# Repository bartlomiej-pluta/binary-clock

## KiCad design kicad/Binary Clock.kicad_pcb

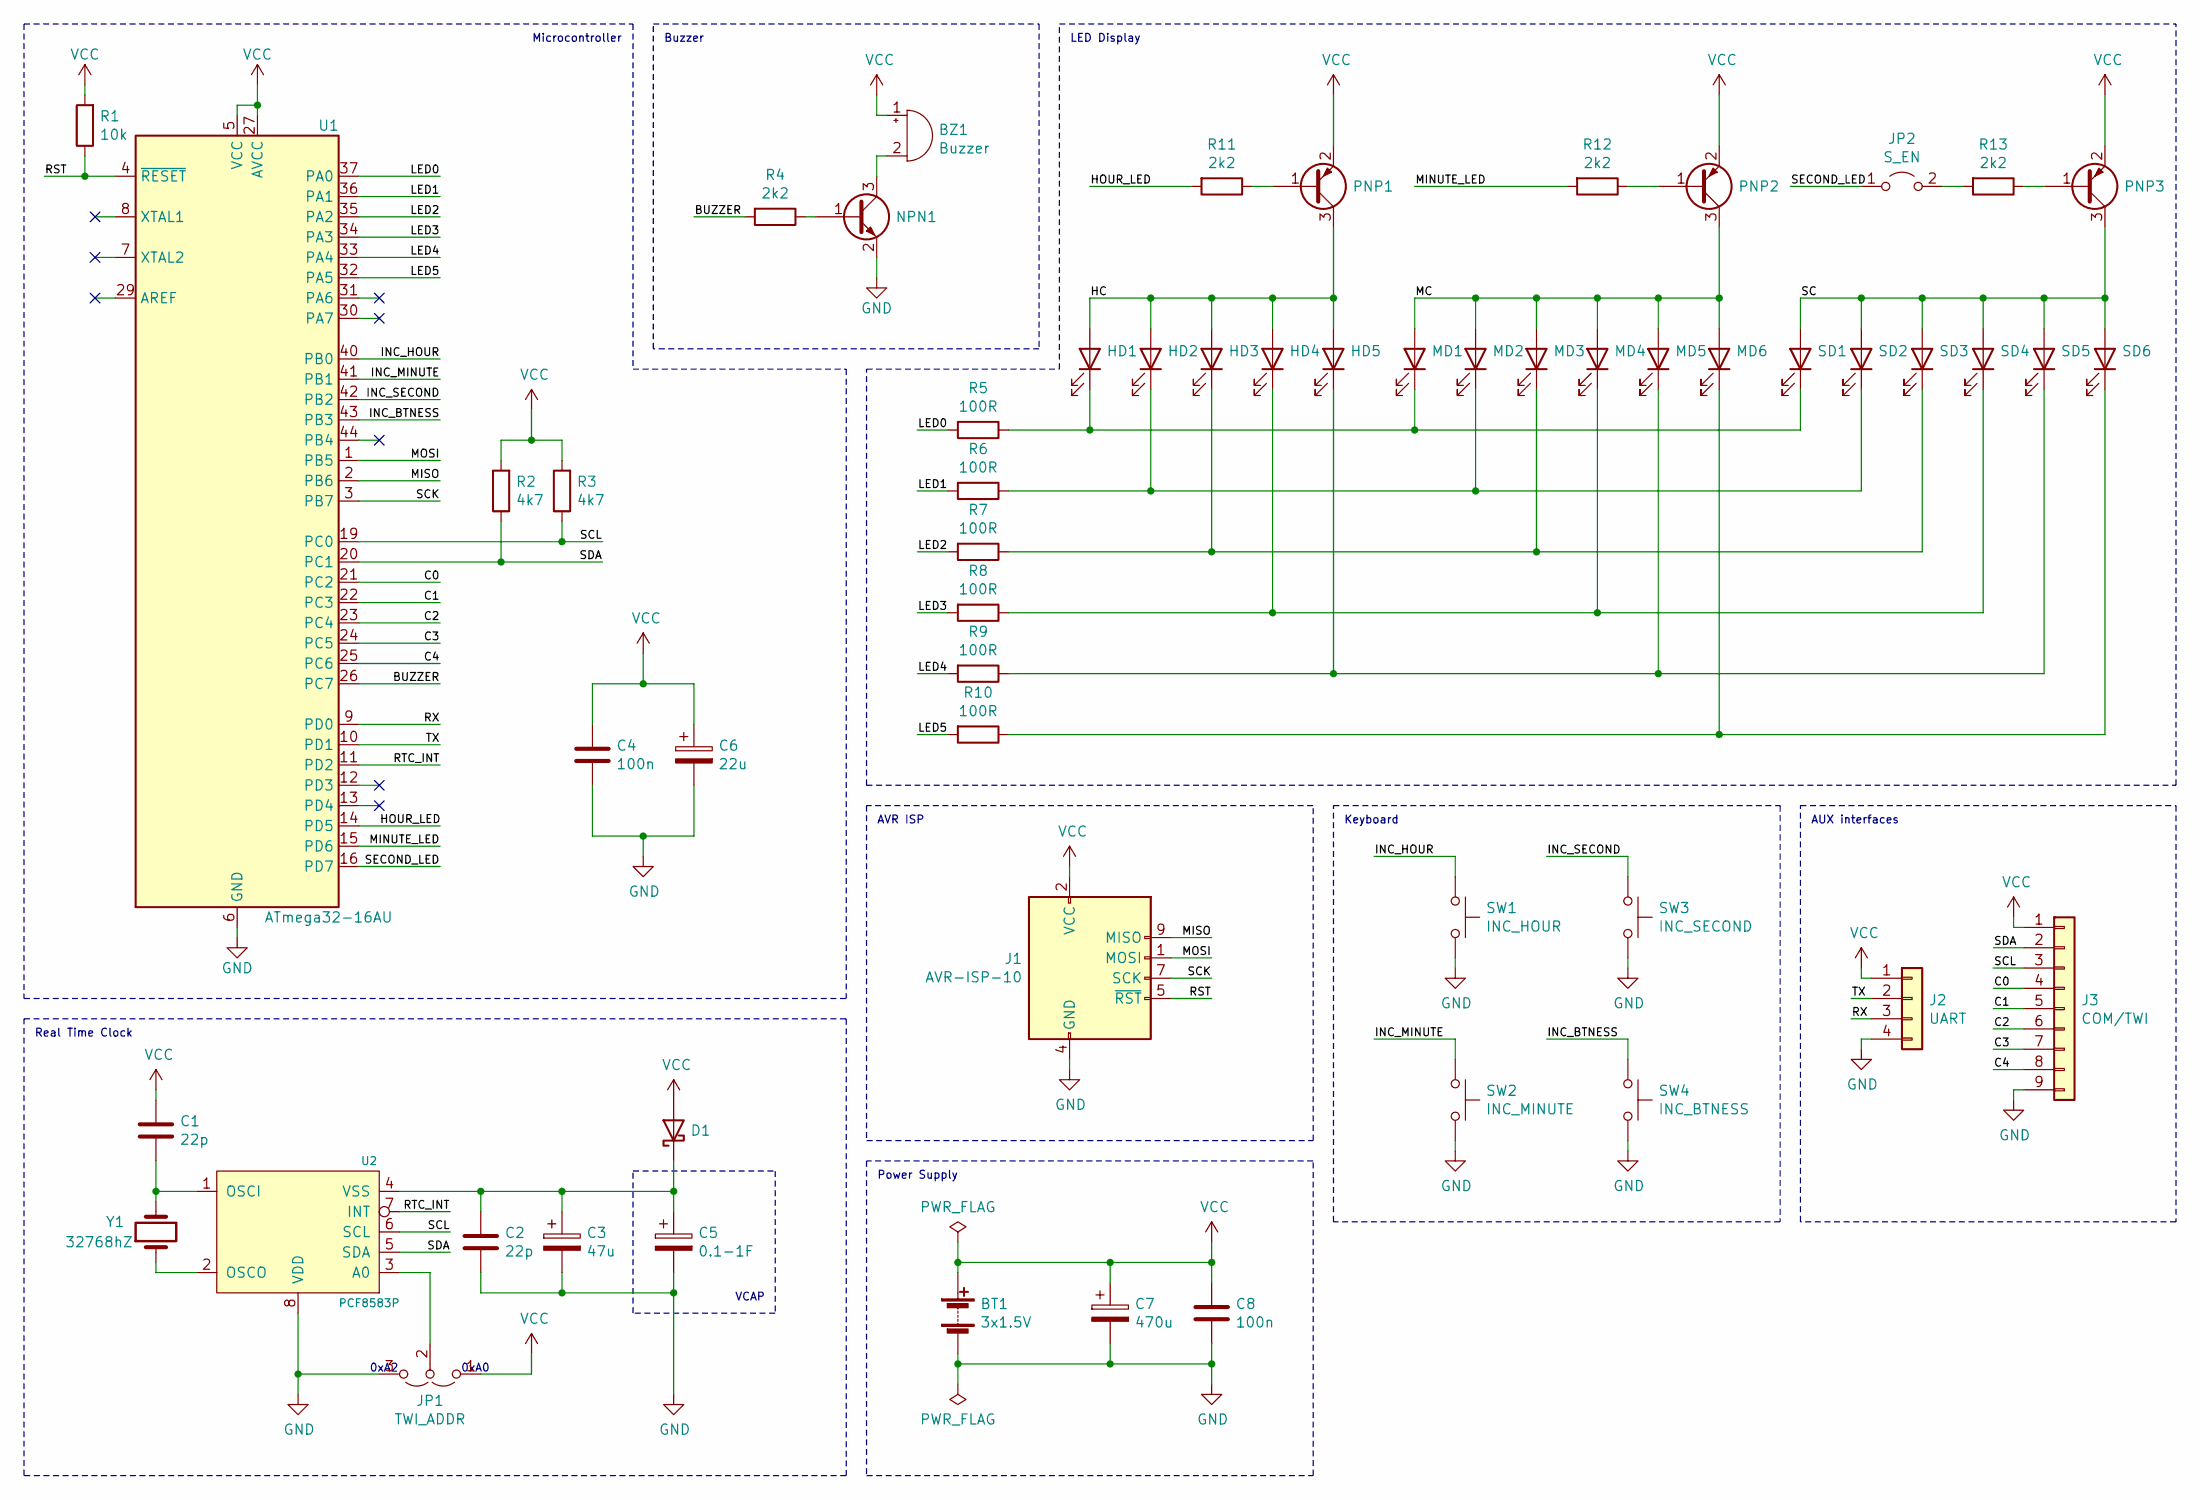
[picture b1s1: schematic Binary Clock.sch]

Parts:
BT1: 3x1.5V; BatteryPackage
BZ1: Buzzer; Buzzer_12x9.5RM7.6
C1, C2: 22p; C_0805_2012Metric_Pad1.18x1.45mm_HandSolder
C3: 47u; CP_Elec_6.3x5.3
C4, C8: 100n; C_0805_2012Metric_Pad1.18x1.45mm_HandSolder
C5: 0.1-1F; SuperCapacitor
C6: 22u; CP_Elec_4x3
C7: 470u; CP_Elec_8x10
D1: D_Schottky; D_2114_3652Metric
HD1, HD2, HD3, HD4, HD5: LED; LED_D5.0mm
J1: AVR-ISP-10; IDC-Header_2x05_P2.54mm_Vertical
J2: UART; PinHeader_1x04_P2.54mm_Vertical
J3: COM/TWI; PinHeader_1x09_P2.54mm_Vertical
JP1: TWI_ADDR; PinHeader_1x03_P2.54mm_Horizontal
JP2: S_EN; PinHeader_1x02_P2.54mm_Vertical
MD1, MD2, MD3, MD4, MD5, MD6: LED; LED_D5.0mm
NPN1: Q_NPN_BEC; SOT-23
PNP1, PNP2, PNP3: Q_PNP_BEC; SOT-23
R1: 10k; R_1206_3216Metric_Pad1.30x1.75mm_HandSolder
R2, R3: 4k7; R_1206_3216Metric_Pad1.30x1.75mm_HandSolder
R4, R11, R12, R13: 2k2; R_1206_3216Metric_Pad1.30x1.75mm_HandSolder
R5, R6, R7, R8, R9, R10: 100R; R_1206_3216Metric_Pad1.30x1.75mm_HandSolder
SD1, SD2, SD3, SD4, SD5, SD6: LED; LED_D5.0mm
SW1: INC_HOUR; SW_PUSH_6mm
SW2: INC_MINUTE; SW_PUSH_6mm
SW3: INC_SECOND; SW_PUSH_6mm
SW4: INC_BTNESS; SW_PUSH_6mm
U1: ATmega32-16AU; TQFP-44_10x10mm_P0.8mm
U2: PCF8583P; SOT176-1
Y1: 32768hZ; Crystal_DS26_D2.0mm_L6.0mm_Horizontal

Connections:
/BUZZER: R4.2, U1.26 (PC7)
/C0: J3.4, U1.21 (PC2)
/C1: J3.5, U1.22 (PC3)
/C2: J3.6, U1.23 (PC4)
/C3: J3.7, U1.24 (PC5)
/C4: J3.8, U1.25 (PC6)
/HC: HD1.2 (A), HD2.2 (A), HD3.2 (A), HD4.2 (A), HD5.2 (A), PNP1.3 (C)
/HOUR_LED: R11.2, U1.14 (PD5)
/INC_BTNESS: SW4.1, U1.43 (PB3)
/INC_HOUR: SW1.1, U1.40 (PB0)
/INC_MINUTE: SW2.1, U1.41 (PB1)
/INC_SECOND: SW3.1, U1.42 (PB2)
/LED0: R5.2, U1.37 (PA0)
/LED1: R6.2, U1.36 (PA1)
/LED2: R7.2, U1.35 (PA2)
/LED3: R8.2, U1.34 (PA3)
/LED4: R9.2, U1.33 (PA4)
/LED5: R10.2, U1.32 (PA5)
/MC: MD1.2 (A), MD2.2 (A), MD3.2 (A), MD4.2 (A), MD5.2 (A), MD6.2 (A), PNP2.3 (C)
/MINUTE_LED: R12.2, U1.15 (PD6)
/MISO: J1.9 (MISO), U1.2 (PB6)
/MOSI: J1.1 (MOSI), U1.1 (PB5)
/RST: J1.5 (~RST), R1.1, U1.4 (~RESET)
/RTC_INT: U1.11 (PD2), U2.7 (INT)
/RX: J2.3, U1.9 (PD0)
/SC: PNP3.3 (C), SD1.2 (A), SD2.2 (A), SD3.2 (A), SD4.2 (A), SD5.2 (A), SD6.2 (A)
/SCK: J1.7 (SCK), U1.3 (PB7)
/SCL: J3.3, R3.1, U1.19 (PC0), U2.6 (SCL)
/SDA: J3.2, R2.1, U1.20 (PC1), U2.5 (SDA)
/SECOND_LED: JP2.1 (A), U1.16 (PD7)
/TX: J2.2, U1.10 (PD1)
GND: BT1.2 (-), C2.2, C3.2, C4.2, C5.2, C6.2, C7.2, C8.2, J1.4 (GND), J1.6 (GND), J1.8 (GND), J1.10 (GND), J2.4, J3.9, JP1.3 (B), NPN1.2 (E), SW1.2, SW2.2, SW3.2, SW4.2, U1.6 (GND), U1.18 (GND), U1.28 (GND), U1.39 (GND), U2.8 (VDD)
unnamed: BZ1.2 (+), NPN1.3 (C)
unnamed: C1.2, U2.1 (OSCI), Y1.2
unnamed: C2.1, C3.1, C5.1, D1.1 (K), U2.4 (VSS)
unnamed: HD1.1 (K), MD1.1 (K), R5.1, SD1.1 (K)
unnamed: HD2.1 (K), MD2.1 (K), R6.1, SD2.1 (K)
unnamed: HD3.1 (K), MD3.1 (K), R7.1, SD3.1 (K)
unnamed: HD4.1 (K), MD4.1 (K), R8.1, SD4.1 (K)
unnamed: HD5.1 (K), MD5.1 (K), R9.1, SD5.1 (K)
unnamed: JP1.2 (C), U2.3 (A0)
unnamed: JP2.2 (B), R13.2
unnamed: MD6.1 (K), R10.1, SD6.1 (K)
unnamed: NPN1.1 (B), R4.1
unnamed: PNP1.1 (B), R11.1
unnamed: PNP2.1 (B), R12.1
unnamed: PNP3.1 (B), R13.1
unnamed: U2.2 (OSCO), Y1.1
VCC: BT1.1 (+), BZ1.1 (-), C1.1, C4.1, C6.1, C7.1, C8.1, D1.2 (A), J1.2 (VCC), J2.1, J3.1, JP1.1 (A), PNP1.2 (E), PNP2.2 (E), PNP3.2 (E), R1.2, R2.2, R3.2, U1.5 (VCC), U1.17 (VCC), U1.27 (AVCC), U1.38 (VCC)

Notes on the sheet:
VCAP
LED Display
AVR ISP
Real Time Clock
Power Supply
Keyboard
AUX interfaces
Microcontroller
Buzzer
0xA2
0xA0

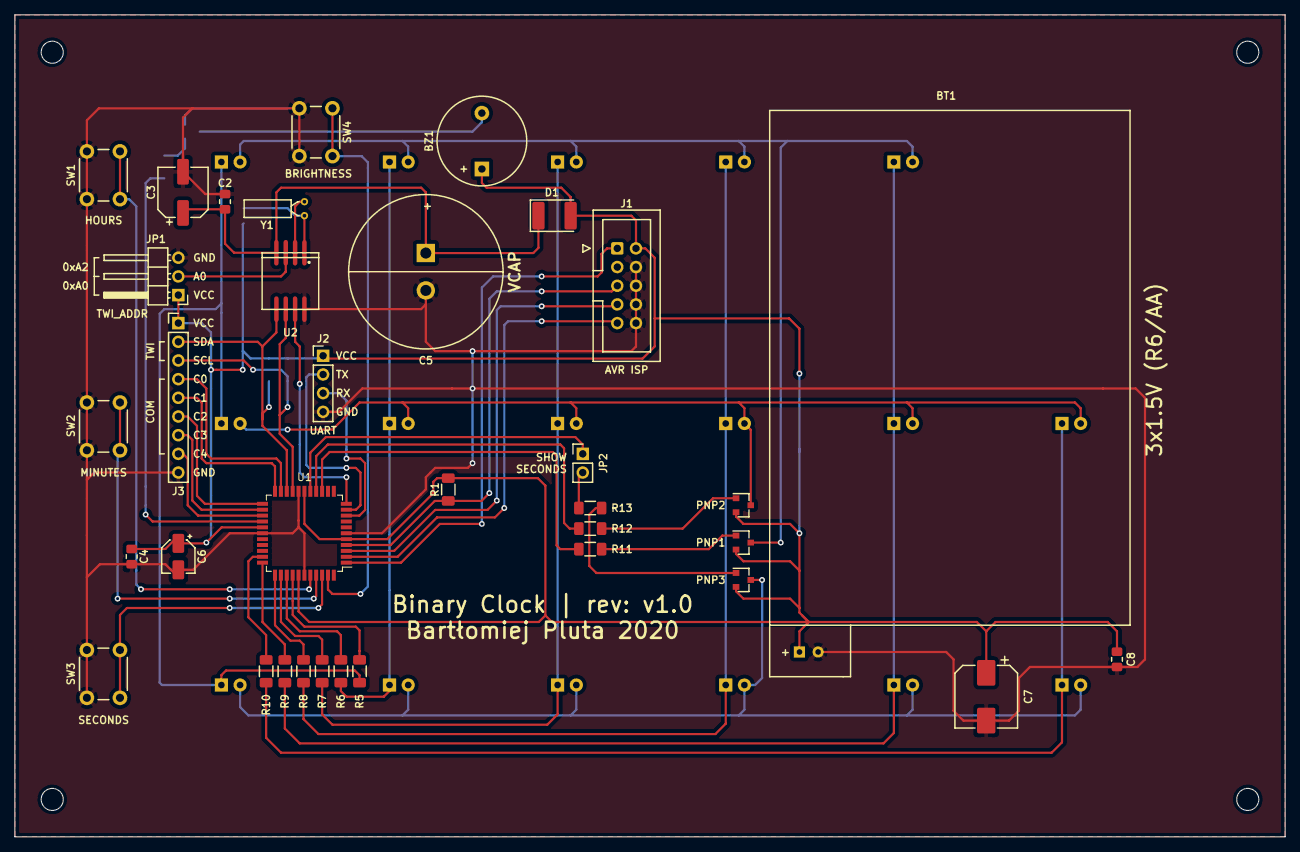
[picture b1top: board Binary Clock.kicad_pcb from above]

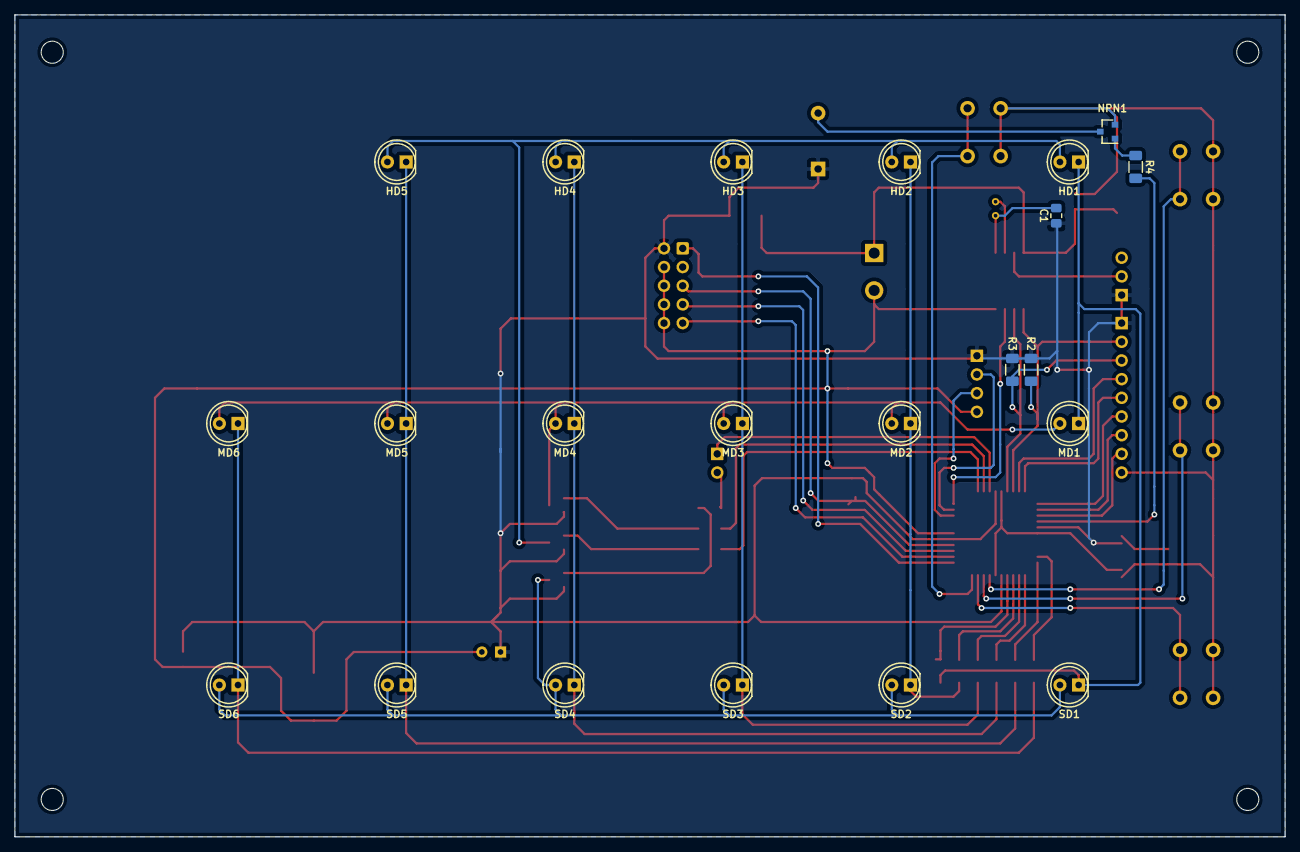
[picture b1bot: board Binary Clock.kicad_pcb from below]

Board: 2 copper layers, 172.7 x 111.8 mm, 57 parts (22 on the bottom side), 49 nets.

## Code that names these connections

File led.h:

#ifndef __LED_H__
#define __LED_H__

#define LED0_PORT PORTA
#define LED0_DIR DDRA
#define LED0 (1<<0)
#define LED1_PORT PORTA
#define LED1_DIR DDRA
#define LED1 (1<<1)
#define LED2_PORT PORTA
#define LED2_DIR DDRA
#define LED2 (1<<2)
#define LED3_PORT PORTA
#define LED3_DIR DDRA
#define LED3 (1<<3)
#define LED4_PORT PORTA
#define LED4_DIR DDRA
#define LED4 (1<<4)
#define LED5_PORT PORTA
#define LED5_DIR DDRA
#define LED5 (1<<5)

#define ANODES_PORT PORTD
#define ANODES_DIR DDRD
#define HOUR_ANODE (1<<PD5)
#define MINUTE_ANODE (1<<PD6)
#define SECOND_ANODE (1<<PD7)

extern volatile uint8_t led_hour;
extern volatile uint8_t led_minute;
extern volatile uint8_t led_second;

void led_init(void);

#endif

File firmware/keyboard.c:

#include <avr/io.h>
#include "common.h"
#include "config.h"
#include "keyboard.h"
#include "buzzer.h"
#include "debounce.h"
#include "rtc.h"
#include "led.h"

uint8_t k_inc_hour, k_inc_minute, k_inc_second, k_inc_brightness;

void inc_hour(void)
{  
  rtc_inc_time(HOUR);
  buz_on();
}

void inc_minute(void)
{  
  rtc_inc_time(MINUTE);
  buz_on();
}

void inc_second(void)
{  
  rtc_inc_time(SECOND);
  buz_on();
}

void inc_brightness(void)
{  
  if(++ram_cfg.led_btnes > 7) ram_cfg.led_btnes = 0;
  led_set_btnes(ram_cfg.led_btnes);
  dump_ram2eem();
  buz_on();
}

void kbd_init(void)
{
  R_DDR(KEYBOARD_PORT) &= ~(1<<KEY_INC_HOUR | 1<<KEY_INC_MINUTE | 1<<KEY_INC_SECOND | 1<<KEY_INC_BRIGHTNESS);
  R_PORT(KEYBOARD_PORT) |= 1<<KEY_INC_HOUR | 1<<KEY_INC_MINUTE | 1<<KEY_INC_SECOND | 1<<KEY_INC_BRIGHTNESS;
}

void kbd_handle_event(void)
{
  SuperDebounce(&k_inc_hour, &R_PIN(KEYBOARD_PORT), 1<<KEY_INC_HOUR, 20, 50, &inc_hour, &inc_hour);
  SuperDebounce(&k_inc_minute, &R_PIN(KEYBOARD_PORT), 1<<KEY_INC_MINUTE, 20, 50, &inc_minute, &inc_minute);
  SuperDebounce(&k_inc_second, &R_PIN(KEYBOARD_PORT), 1<<KEY_INC_SECOND, 20, 50, &inc_second, &inc_second);
  SuperDebounce(&k_inc_brightness, &R_PIN(KEYBOARD_PORT), 1<<KEY_INC_BRIGHTNESS, 20, 50, &inc_brightness, &inc_brightness);
}

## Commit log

2020-11-07 Init repo
2020-11-08 Create library for managing LED binary display
2020-11-08 Create I2C/TWI library and enable it
2020-11-09 Create library for PCF8583 (RTC) and enable it
2020-11-09 Create library for software timers and enable it
2020-11-09 Enable setting the clock time via keyboard
2020-11-13 Move source code to firmware directory
2020-11-13 Create KiCAD project
2020-11-17 Enable software-based LED brightness configuration
2020-11-17 Enable storing LED brightness in EEPROM
2020-11-18 Clean code
2020-11-18 Replace led_hour (etc.) globals with TIME struct
2020-11-18 Add INC_BTNESS button to schema
    INC_BTNESS button is desired to increment LED display brightness
2020-11-18 Add INC_BTNESS button to PCB
2020-11-18 Create simple UART library
2020-11-18 Enable callbacks and CR separator in UART library
2020-11-19 Create UART-based AT commands library
2020-11-19 Add support for night mode
2020-11-19 Move AT-related const strings to progmem
2020-11-19 Create global 'time' variable which holds RTC value
2020-11-19 Refactor AT commands
2020-11-19 Create common.h file with meta globals
2020-11-19 Update schema and PCB design
2020-11-21 Refactor code
2020-11-21 Major refactor of RTC-related code
2020-11-21 Add support for weekdays
2020-11-22 Fix warnings in RTC module
2020-11-22 Fix ATI command
2020-11-23 Introduce CPP macros for AVR IN/OUT registers
2020-11-23 Add support for buzzer
2020-11-24 Change goldpins to 2.56mm
2020-11-24 Enable action reapating for keyboard
2020-12-03 Update PCB footprints
2020-12-03 Fix some issues on PCB
2020-12-05 Fix some issues and text labels on PCB
2020-12-05 Fix invalid ATmega footprint
2020-12-05 Improve schema
